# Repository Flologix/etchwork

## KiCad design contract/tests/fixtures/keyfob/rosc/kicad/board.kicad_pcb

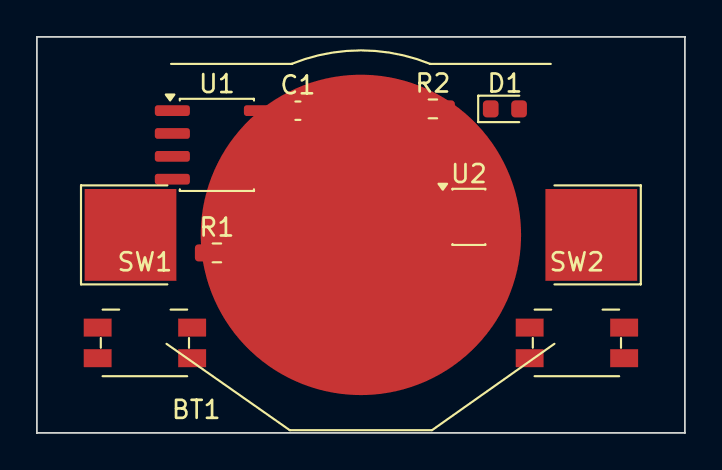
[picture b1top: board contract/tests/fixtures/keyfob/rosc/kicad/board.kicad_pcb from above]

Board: 2 copper layers, 36.0 x 22.0 mm, 9 parts (0 on the bottom side), 7 nets, no tracks yet.

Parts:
BT1: CR2032; BatteryHolder_Keystone_3002_1x2032
C1: 100n; C_0603_1608Metric
D1: RED; LED_0603_1608Metric
R1: 100k; R_0603_1608Metric
R2: 1k; R_0603_1608Metric
SW1, SW2: SW_Push; Panasonic_EVQPUJ_EVQPUA
U1: EV1527; SOIC-8_3.9x4.9mm_P1.27mm
U2: SYN115; SOT-23-6

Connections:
DOUT: R2.1, U1.7 (DOUT), U2.6 (DATA)
GND: BT1.2 (-), C1.2, D1.1 (K), U1.1 (VSS), U2.2 (VSS)
LED_A: D1.2 (A), R2.2
NET3: R1.1, U1.2 (OSC)
N_SW1: SW1.2, U1.3 (K0)
N_SW2: SW2.2, U1.4 (K1)
VCC: BT1.1 (+), C1.1, R1.2, SW1.1, SW2.1, U1.8 (VDD), U2.5 (VDD)

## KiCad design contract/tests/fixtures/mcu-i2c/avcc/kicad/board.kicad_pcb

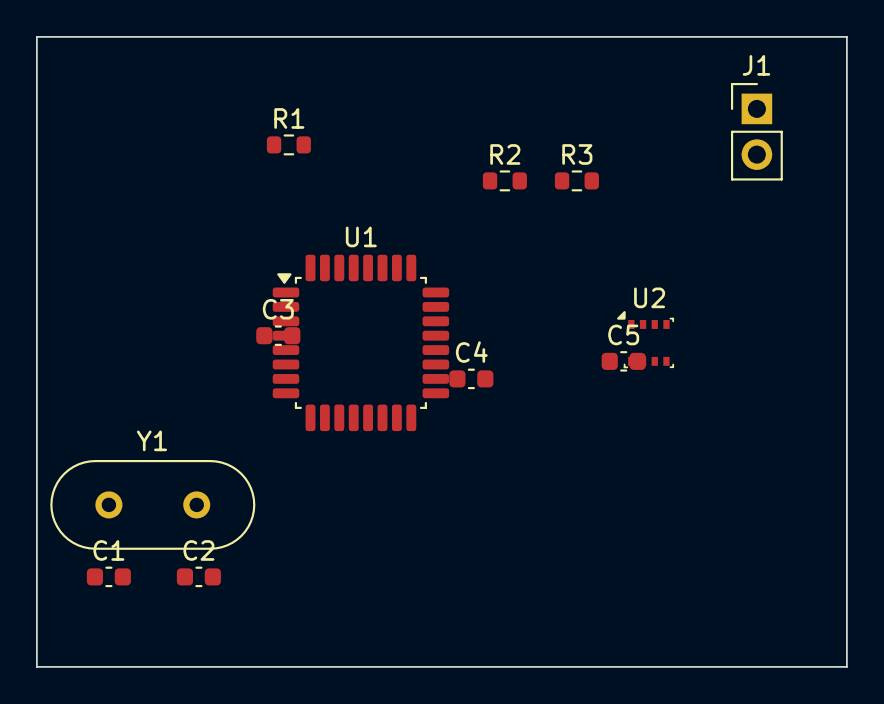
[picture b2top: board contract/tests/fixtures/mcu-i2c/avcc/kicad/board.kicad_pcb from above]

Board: 2 copper layers, 45.0 x 35.0 mm, 12 parts (0 on the bottom side), 8 nets, no tracks yet.

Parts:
C1, C2: 22p; C_0603_1608Metric
C3, C4, C5: 100n; C_0603_1608Metric
J1: Conn_01x02; PinHeader_1x02_P2.54mm_Vertical
R1: 10k; R_0603_1608Metric
R2, R3: 4.7k; R_0603_1608Metric
U1: ATmega328P-AU; TQFP-32_7x7mm_P0.8mm
U2: BME280; Bosch_LGA-8_2.5x2.5mm_P0.65mm_ClockwisePinNumbering
Y1: 8MHz; Crystal_HC49-4H_Vertical

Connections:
+3V3: C3.1, C5.1, J1.1, R1.2, R2.2, R3.2, U1.4 (VCC), U1.6 (VCC), U2.2 (CSB), U2.6 (VDDIO), U2.8 (VDD)
AVCC_X: C4.1, U1.18 (AVCC)
GND: C1.2, C2.2, C3.2, C4.2, C5.2, J1.2, U1.3 (GND), U1.5 (GND), U1.21 (GND), U2.1 (GND), U2.5 (SDO), U2.7 (GND)
N_RST: R1.1, U1.29 (~RESET/PC6)
N_SCL: R3.1, U1.28 (SCL/PC5), U2.4 (SCK)
N_SDA: R2.1, U1.27 (SDA/PC4), U2.3 (SDI)
XT1: C1.1, U1.7 (XTAL1/PB6), Y1.1
XT2: C2.1, U1.8 (XTAL2/PB7), Y1.2
